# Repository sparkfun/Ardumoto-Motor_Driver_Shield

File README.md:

SparkFun Ardumoto - Motor Driver Shield
=======================================

[*SparkFun Ardumoto - Motor Driver Shield (DEV-14129)*](https://www.sparkfun.com/products/14129)

This is a motor shield for Arduino that will control two DC motors. 
Based on the L298 H-bridge, the SparkFun Ardumoto can drive up to 2 amps per channel. 

Repository Contents
-------------------
* **/Firmware** - Example Arduino sketch
* **/Hardware** - All Eagle design files (.brd, .sch)

Documentation
--------------
* [Hookup Guide](https://learn.sparkfun.com/tutorials/ardumoto-kit-hookup-guide)

Version History
---------------

* [HW_1.4_FW_1.0](https://github.com/sparkfun/Ardumoto-Motor_Driver_Shield/tree/HW_1.4_FW_1.0) - Version 1.4
* [V_2.0.0](https://github.com/sparkfun/Ardumoto-Motor_Driver_Shield/tree/V_2.0.0) - Initial build release
* [V_2.0.1](https://github.com/sparkfun/Ardumoto-Motor_Driver_Shield/tree/V_2.0.1) - Public release

License Information
-------------------
The hardware is released under [Creative Commons ShareAlike 4.0 International](https://creativecommons.org/licenses/by-sa/4.0/).
The code is beerware; if you see me (or any other SparkFun employee) at the local, and you've found our code helpful, please buy us a round!

Distributed as-is; no warranty is given.

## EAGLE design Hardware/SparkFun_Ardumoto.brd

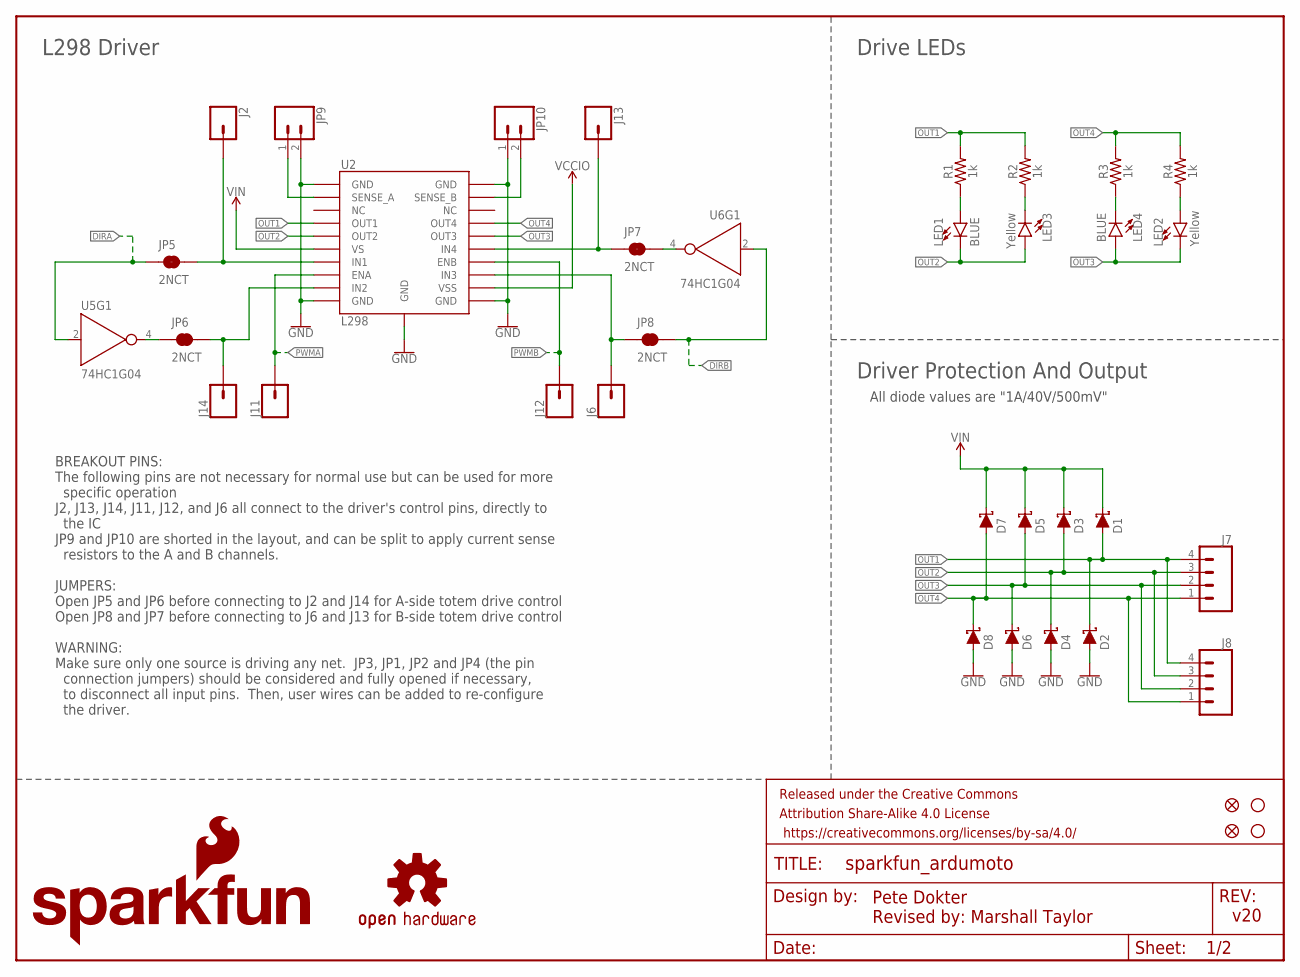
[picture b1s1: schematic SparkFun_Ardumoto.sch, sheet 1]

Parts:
D1, D2, D3, D4, D5, D6, D7, D8: 1A/40V/500mV; SMA-DIODE
FD1, FD2: FIDUCIALUFIDUCIAL; MICRO-FIDUCIAL
FRAME2: FRAME-LETTERNO_PACKAGE; DUMMY
H1, H2: STAND-OFF
J2, J6, J11, J12, J13, J14: CONN_01PTH_NO_SILK_YES_STOP; 1X01_NO_SILK
J7: CONN_04SCREW; SCREWTERMINAL-3.5MM-4
J8: CONN_04; 1X04
JP5, JP6, JP7, JP8: 2NCT; SMT-JUMPER_2_NC_TRACE_SILK
JP9, JP10: CONN_021X02_NO_SILK; 1X02_NO_SILK
LED1, LED4: BLUE; LED-0603
LED2, LED3: Yellow; LED-0603
LOGO2: SFE_LOGO_NAME_FLAME.1_INCH; SFE_LOGO_NAME_FLAME_.1
R1, R2, R3, R4: 1k; 0603
U2: L298; POWERSO20_L298_PAD
U5, U6: 74HC1G04; SOT353
U$1: OSHW-LOGOS; OSHW-LOGO-S

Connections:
DIRA: JP5.1, U5.2 (A); also elsewhere on the board
DIRB: JP8.2, U6.2 (A); also elsewhere on the board
GND: D2.A, D4.A, D6.A, D8.A, JP9.2, JP10.1, U2.1 (GND), U2.10 (GND), U2.11 (GND), U2.20 (GND), U2.PAD (GND); also elsewhere on the board
IN1: J2.1, JP5.2, U2.7 (IN1)
IN2: J14.1, JP6.2, U2.9 (IN2)
IN3: J6.1, JP8.1, U2.13 (IN3)
IN4: J13.1, JP7.1, U2.15 (IN4)
unnamed: LED1.A, R1.1
unnamed: LED3.C, R2.1
unnamed: LED4.C, R3.1
unnamed: LED2.A, R4.1
NDIRA: JP6.1, U5.4 (Y)
NDIRB: JP7.2, U6.4 (Y)
OUT1: D1.A, D2.C, J7.4, J8.4, R1.2, R2.2, U2.4 (OUT1)
OUT2: D3.A, D4.C, J7.3, J8.3, LED1.C, LED3.A, U2.5 (OUT2)
OUT3: D5.A, D6.C, J7.2, J8.2, LED2.C, LED4.A, U2.16 (OUT3)
OUT4: D7.A, D8.C, J7.1, J8.1, R3.2, R4.2, U2.17 (OUT4)
PWMA: J11.1, U2.8 (ENA); also elsewhere on the board
PWMB: J12.1, U2.14 (ENB); also elsewhere on the board
SENA: JP9.1, U2.2 (SENSE_A)
SENB: JP10.2, U2.19 (SENSE_B)
VCCIO: U2.12 (VSS); also elsewhere on the board
VIN: D1.C, D3.C, D5.C, D7.C, U2.6 (VS); also elsewhere on the board

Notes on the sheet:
v20
Revised by: Marshall Taylor
Pete Dokter
BREAKOUT PINS: The following pins are not necessary for normal use but can be used for more specific operation J2, J13, J14, J11, J12, and J6 all connect to the driver's control pins, directly to the IC JP9 and JP10 are shorted in the layout, and can be split to apply current sense resistors to the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
L298 Driver
Driver Protection And Output
Drive LEDs
All diode values are "1A/40V/500mV"

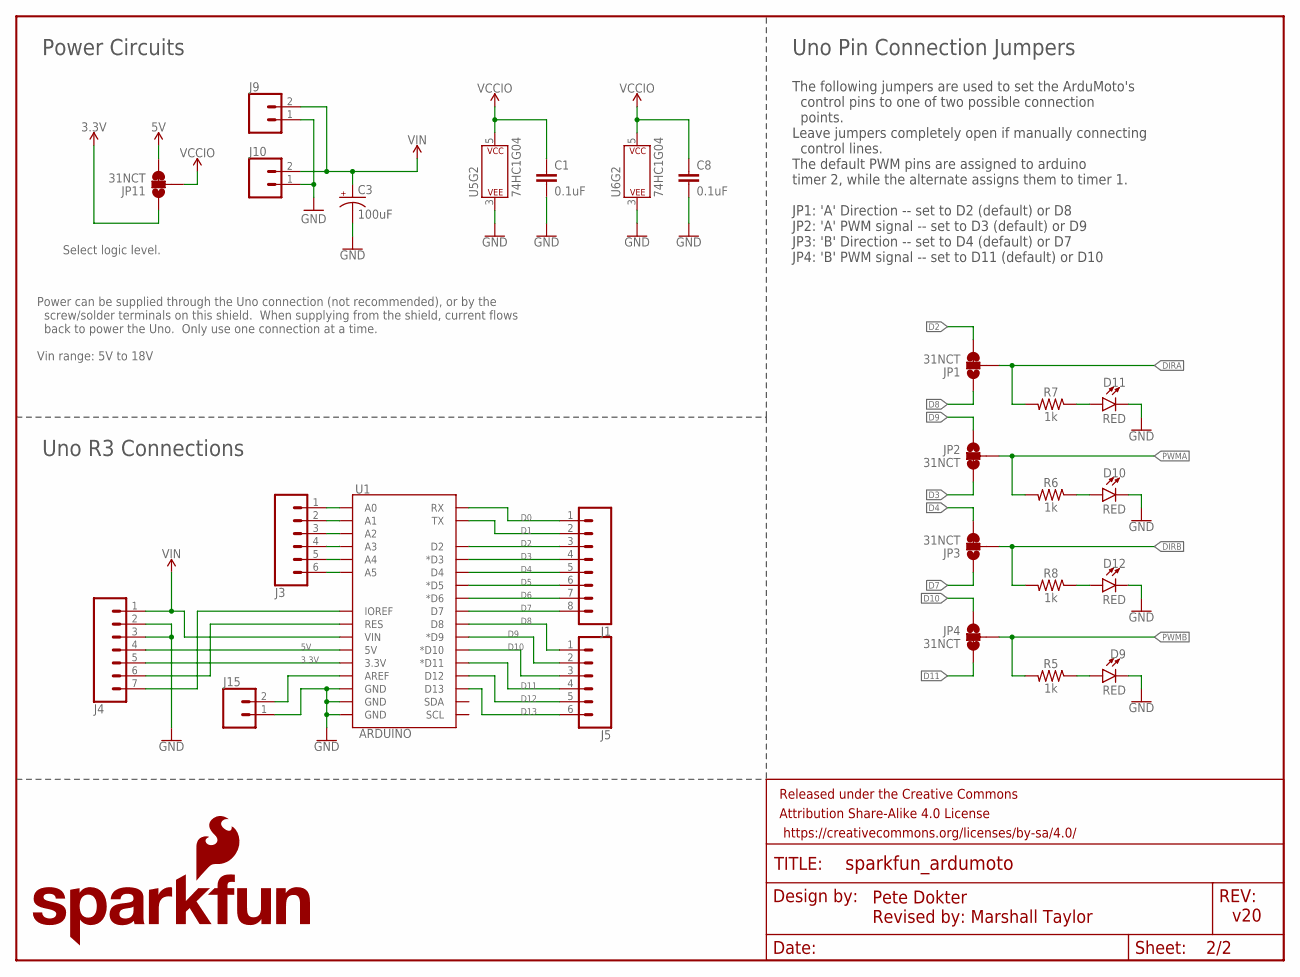
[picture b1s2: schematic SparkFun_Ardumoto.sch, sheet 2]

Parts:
C1, C8: 0.1uF; 0603
C3: 100uF; PANASONIC_D
D9, D10, D11, D12: RED; LED-0603
FRAME1: FRAME-LETTER; CREATIVE_COMMONS
J1: CONN_08NO_SILK_FEMALE_PTH; 1X08_NO_SILK
J3, J5: CONN_06NO_SILK_FEMALE_PTH; 1X06_NO_SILK
J4: CONN_07NO_SILK; 1X07_NO_SILK
J9: CONN_02; 1X02
J10: CONN_023.5MM; SCREWTERMINAL-3.5MM-2
J15: CONN_021X02_NO_SILK; 1X02_NO_SILK
JP1, JP2, JP3, JP4, JP11: 31NCT; SMT-JUMPER_3_1-NC_TRACE_SILK
LOGO1: SFE_LOGO_NAME_FLAME.2_INCH; SFE_LOGO_NAME_FLAME_.2
R5, R6, R7, R8: 1k; 0603
U1: ARDUINO; UNO_R3_SHIELD_NOLABELS
U5, U6: 74HC1G04; SOT353

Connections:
3.3V: J4.5, JP11.1, U1.3.3V
5V: J4.4, JP11.3, U1.5V
D0: J1.1, U1.RX
D1: J1.2, U1.TX
D2: J1.3, JP1.3, U1.D2
D3: J1.4, JP2.3, U1.D3 (*D3)
D4: J1.5, JP3.3, U1.D4
D5: J1.6, U1.D5 (*D5)
D6: J1.7, U1.D6 (*D6)
D7: J1.8, JP3.1, U1.D7
D8: J5.1, JP1.1, U1.D8
D9: J5.2, JP2.1, U1.D9 (*D9)
D10: J5.3, JP4.1, U1.D10 (*D10)
D11: J5.4, JP4.3, U1.D11 (*D11)
D12: J5.5, U1.D12
D13: J5.6, U1.D13
DIRA: JP1.2, R7.2; also elsewhere on the board
DIRB: JP3.2, R8.2; also elsewhere on the board
GND: C1.2, C3.-, C8.2, D9.C, D10.C, D11.C, D12.C, J4.2, J4.3, J9.1, J10.1, J15.1, U1.GND@0 (GND), U1.GND@1 (GND), U1.GND@2 (GND), U5.3 (P$V-), U6.3 (P$V-); also elsewhere on the board
IOREF: J4.7, U1.IOREF
unnamed: J15.2, U1.AREF
unnamed: J3.1, U1.A0
unnamed: J3.2, U1.A1
unnamed: J3.3, U1.A2
unnamed: J3.4, U1.A3
unnamed: J3.5, U1.A4
unnamed: J3.6, U1.A5
unnamed: D9.A, R5.1
unnamed: D10.A, R6.1
unnamed: D12.A, R8.1
unnamed: D11.A, R7.1
PWMA: JP2.2, R6.2; also elsewhere on the board
PWMB: JP4.2, R5.2; also elsewhere on the board
RESET: J4.6, U1.RES
VCCIO: C1.1, C8.1, JP11.2, U5.5 (P$V+), U6.5 (P$V+); also elsewhere on the board
VIN: C3.+, J4.1, J9.2, J10.2, U1.VIN; also elsewhere on the board

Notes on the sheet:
Power can be supplied through the Uno connection (not recommended), or by the screw/solder terminals on this shield. When supplying from the shield, current flows back to power the Uno. Only use one connection at a time. Vin range: 5V to 18V
v20
Revised by: Marshall Taylor
The following jumpers are used to set the ArduMoto's control pins to one of two possible connection points. Leave jumpers completely open if manually connecting control lines. The default PWM pins are assigned to arduino timer 2, while the alternate assigns them to timer 1. JP1: 'A' Direction -- se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
Power Circuits
Pete Dokter
Uno Pin Connection Jumpers
Uno R3 Connections
Select logic level.

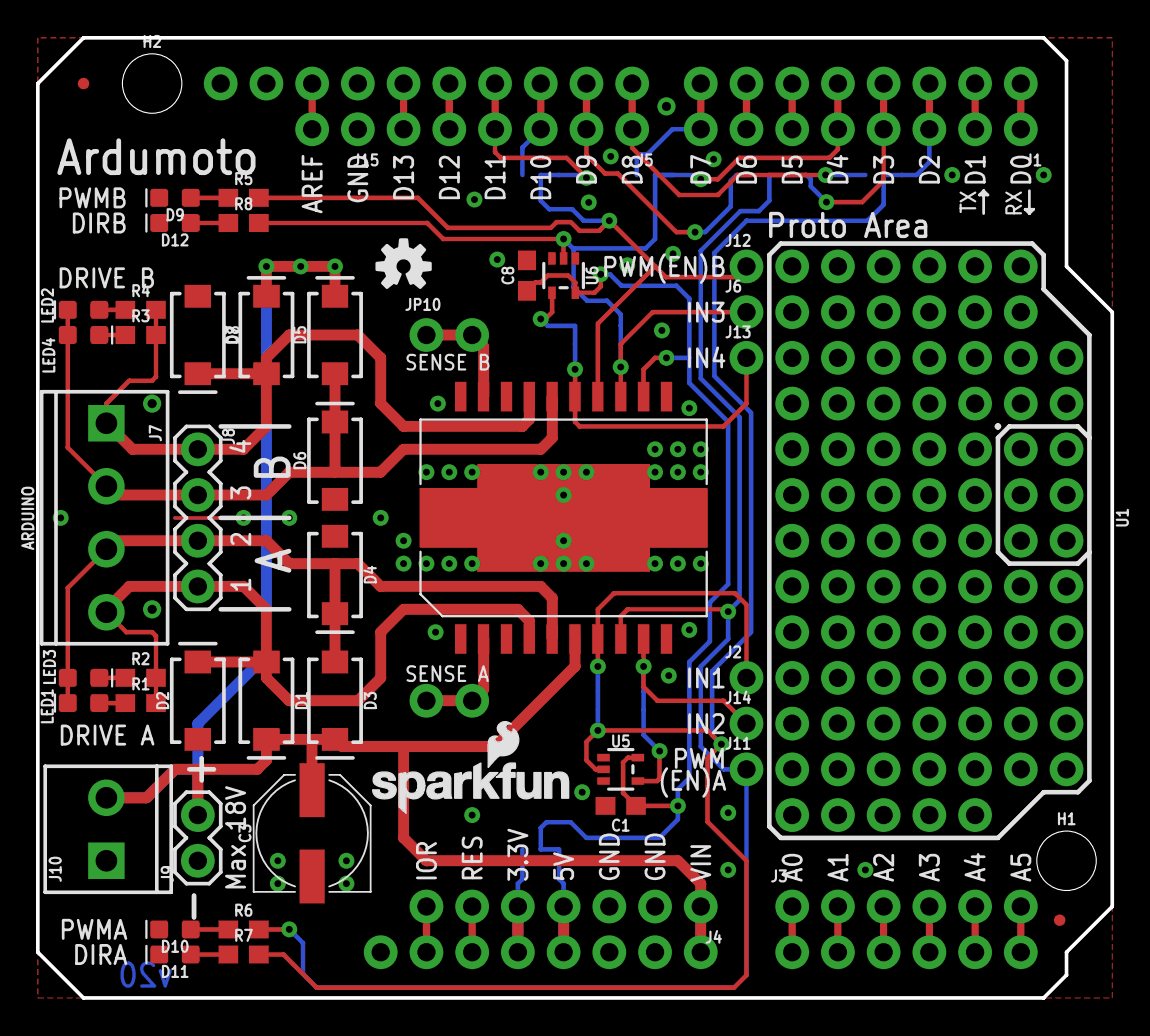
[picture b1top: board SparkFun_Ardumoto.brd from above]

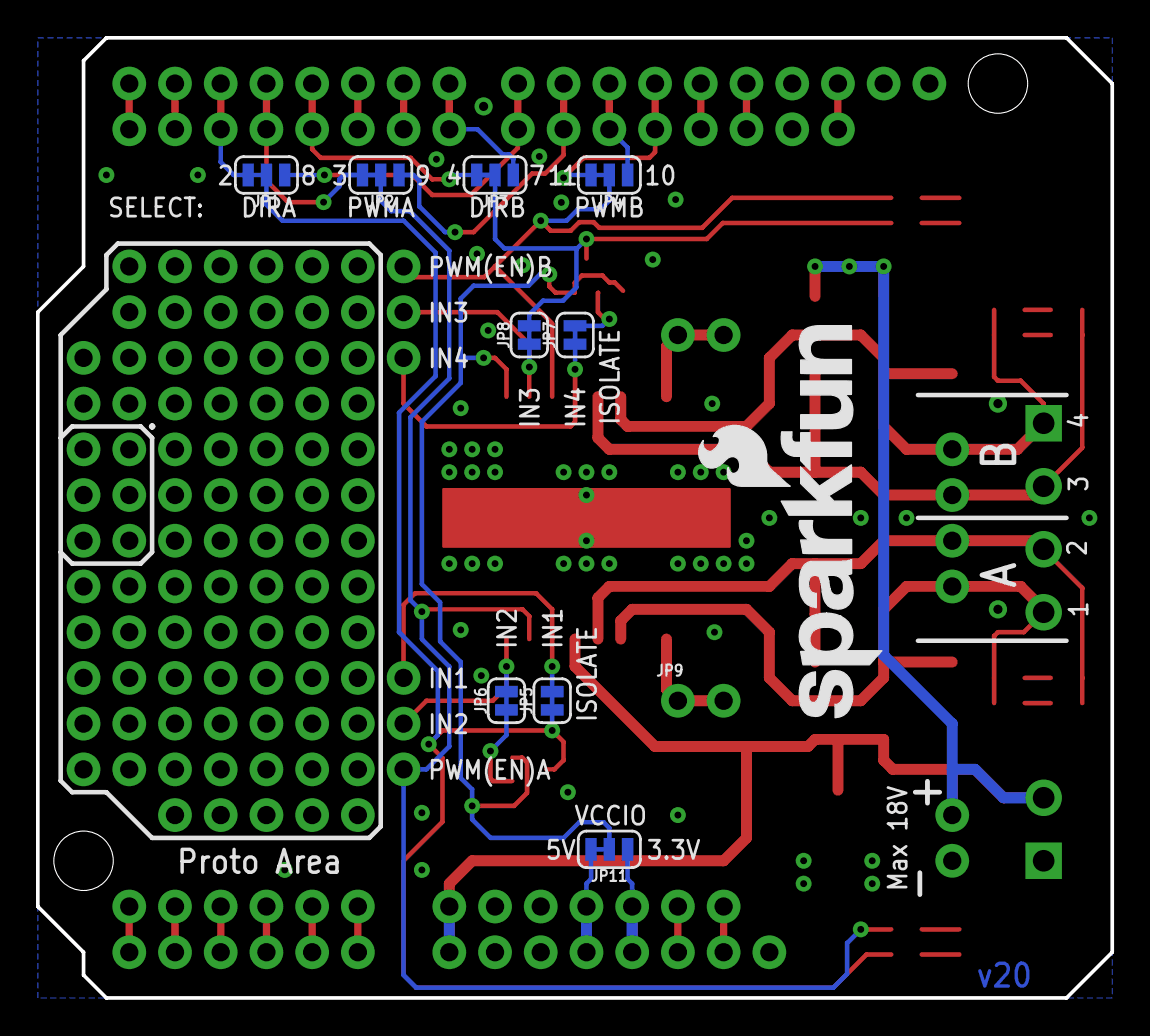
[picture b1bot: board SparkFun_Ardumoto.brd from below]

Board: 2 copper layers, 59.7 x 53.3 mm, 66 parts (11 on the bottom side), 52 nets.

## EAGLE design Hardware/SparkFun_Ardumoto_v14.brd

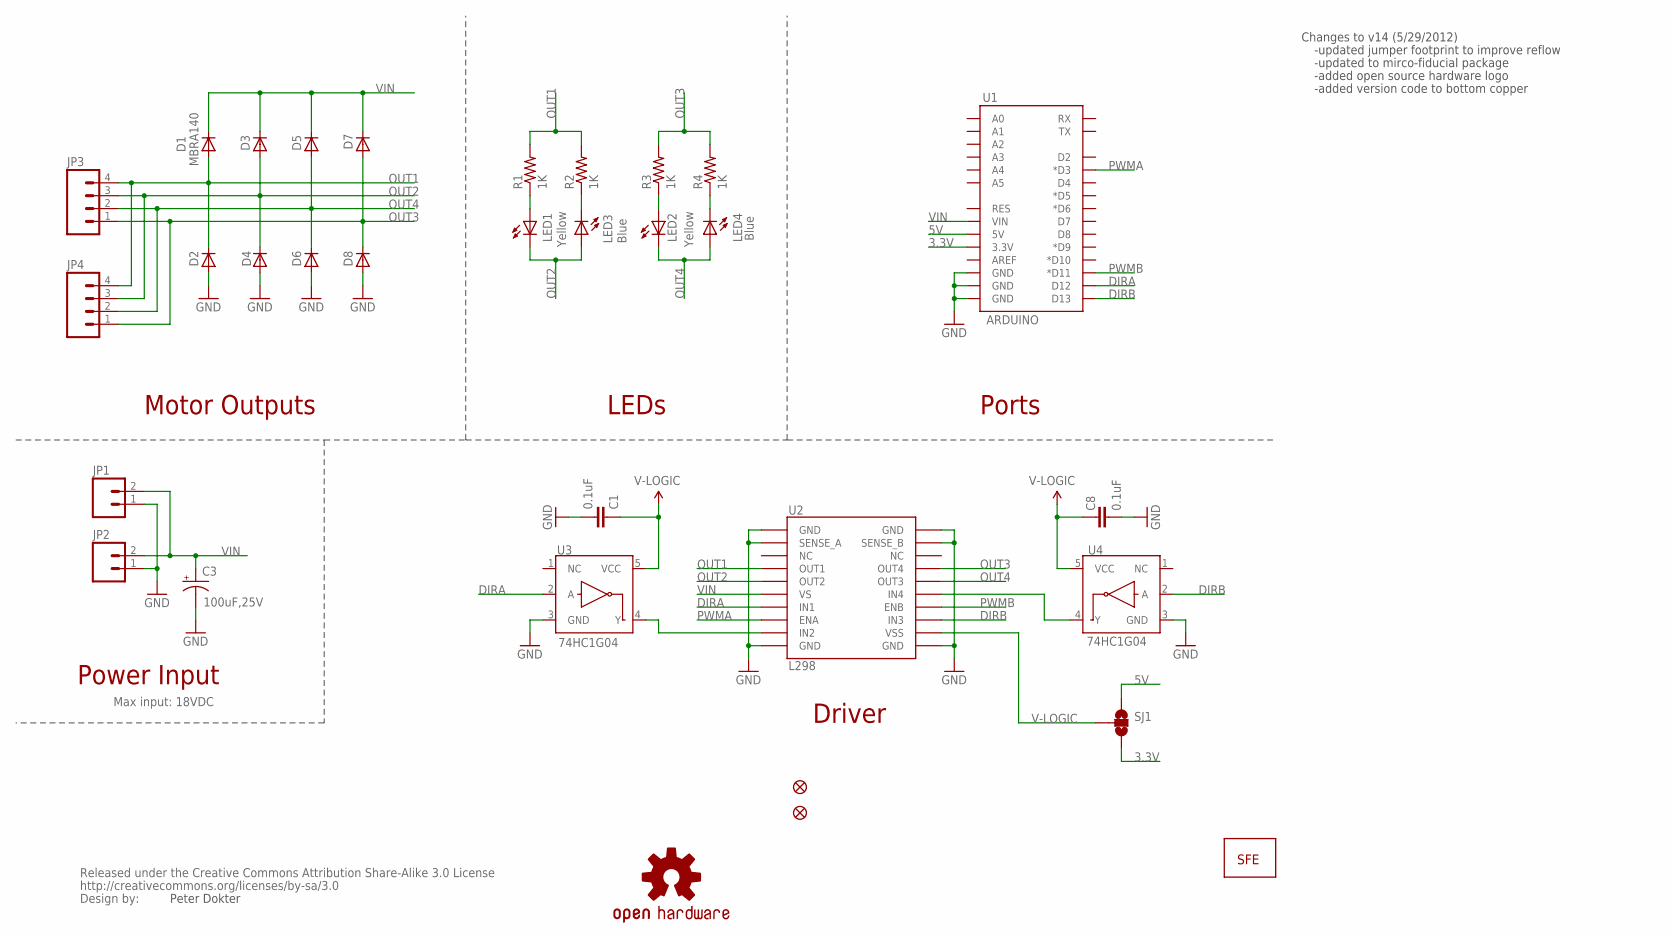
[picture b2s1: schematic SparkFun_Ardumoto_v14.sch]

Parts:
C1, C8: 0.1uF; 0402-CAP
C3: 100uF,25V; NIPPON_F80
D1, D2, D3, D4, D5, D6, D7, D8: MBRA140; SMA-DIODE
JP1: M02PTH; 1X02
JP2: M023.5MM; SCREWTERMINAL-3.5MM-2
JP3: M04SCREW; SCREWTERMINAL-3.5MM-4
JP4: M04PTH; 1X04
JP5, JP6: FIDUCIALUFIDUCIAL; MICRO-FIDUCIAL
LED1, LED2: Yellow; LED-0603
LED3, LED4: Blue; LED-0603
R1, R2, R3, R4: 1K; 0402-RES
SJ1: SOLDERJUMPER_2WAYPASTE1&2; SJ_3_PASTE1&2
U1: ARDUINO; DUEMILANOVE_SHIELD_NOLABELS
U2: L298; POWERSO20
U3, U4: 74HC1G04; SC70
U$1: OSHW-LOGOS; OSHW-LOGO-S
U$10: LOGO-SFENEW; SFE-NEW-WEBLOGO
U$11: CREATIVE_COMMONS

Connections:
3.3V: SJ1.3, U1.3.3V
5V: SJ1.1, U1.5V
DIRA: U1.D12, U2.7 (IN1), U3.2 (A)
DIRB: U1.D13, U2.13 (IN3), U4.2 (A)
GND: C1.2, C3.-, C8.2, D2.A, D4.A, D6.A, D8.A, JP1.1, JP2.1, U1.GND@0 (GND), U1.GND@1 (GND), U1.GND@2 (GND), U2.1 (GND), U2.2 (SENSE_A), U2.10 (GND), U2.11 (GND), U2.19 (SENSE_B), U2.20 (GND), U3.3 (GND), U4.3 (GND)
unnamed: U2.9 (IN2), U3.4 (Y)
unnamed: U2.15 (IN4), U4.4 (Y)
unnamed: LED1.A, R1.1
unnamed: LED3.C, R2.1
unnamed: LED2.A, R3.1
unnamed: LED4.C, R4.1
OUT1: D1.A, D2.C, JP3.4, JP4.4, R1.2, R2.2, U2.4 (OUT1)
OUT2: D3.A, D4.C, JP3.3, JP4.3, LED1.C, LED3.A, U2.5 (OUT2)
OUT3: D7.A, D8.C, JP3.1, JP4.1, R3.2, R4.2, U2.17 (OUT4)
OUT4: D5.A, D6.C, JP3.2, JP4.2, LED2.C, LED4.A, U2.16 (OUT3)
PWMA: U1.D3 (*D3), U2.8 (ENA)
PWMB: U1.D11 (*D11), U2.14 (ENB)
V-LOGIC: C1.1, C8.1, SJ1.2, U2.12 (VSS), U3.5 (VCC), U4.5 (VCC)
VIN: C3.+, D1.C, D3.C, D5.C, D7.C, JP1.2, JP2.2, U1.VIN, U2.6 (VS)

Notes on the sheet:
Motor Outputs
LEDs
Ports
Driver
Peter Dokter
Power Input
Max input: 18VDC
Changes to v14 (5/29/2012)
-updated jumper footprint to improve reflow
-updated to mirco-fiducial package
-added open source hardware logo
-added version code to bottom copper

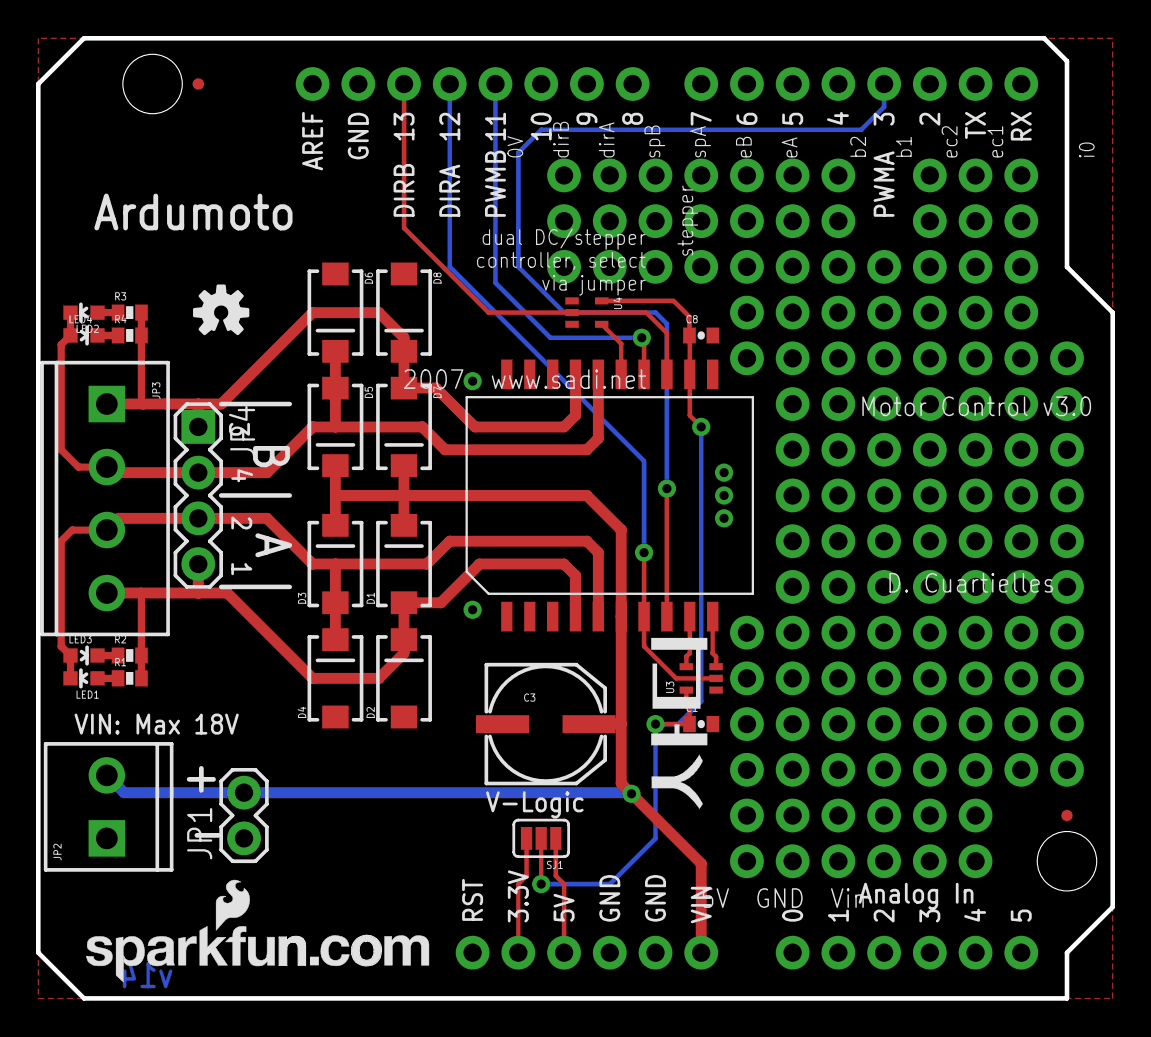
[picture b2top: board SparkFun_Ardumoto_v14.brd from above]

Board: 2 copper layers, 59.7 x 53.3 mm, 33 parts (0 on the bottom side), 19 nets.

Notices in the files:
parts and their libraries:
SparkFun-Connectors: Licensing: Creative Commons ShareAlike 4.0 International - https://creativecommons.org/licenses/by-sa/4.0
SparkFun-Aesthetics: Released under the Creative Commons Attribution Share-Alike 4.0 License
SparkFun-Aesthetics: Released under the Creative Commons
